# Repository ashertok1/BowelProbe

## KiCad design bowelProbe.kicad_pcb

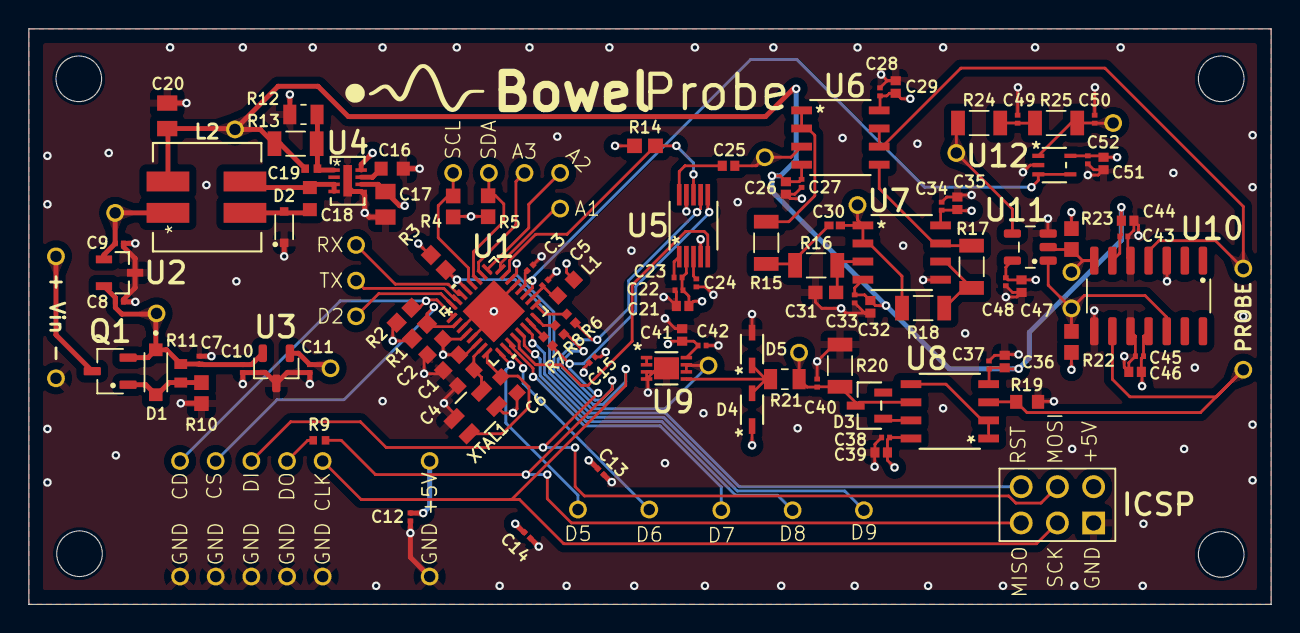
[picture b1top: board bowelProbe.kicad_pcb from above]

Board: 4 copper layers, 87.1 x 40.4 mm, 130 parts (0 on the bottom side), 64 nets.

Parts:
A1, A2, A3: Conn_01x01; CT3149-0
C1, C2, C16, C18: 1u; Cap1uF
C3, C5, C7, C8, C9, C10, C11, C12, C13, C14, C15, C22, C23, C24, C27, C28, C33, C34, C37, C38, C40, C42, C43, C45, C48, C49, C50, C52: 0.1u; Cap0.1uF
C4, C6: 18p; Cap18pF
C17, C20: 4.7u; Cap4.7uF
C19: 4.7p; Cap4.7pF
C21, C25, C26, C29, C32, C35, C36, C39, C41, C44, C46, C47, C51: 10u; Cap10uF
C30: 2.2n; Cap2.2nF
C31: 1n; Cap1nF
D1: BZT52B12
D2: SchottkyDiode; SchottkyReplacement
D2#2, D5, D6, D7, D8, D9: Conn_01x01; CT3149-0
D3: DiodeLowLeak
D4, D5#2: DiodeClamper
ICSP: Conn_02x03_Odd_Even; Dupont2x3
J1, J2: Conn_01x08; microSD
J17: Conn_01x01; CT3149-0
J18, J19, J20, J21, J22, J23, J24, J27, J28, J29, J30, J31, J32: Conn_01x01; CT3149-2
J25, J26: Conn_01x01; CT3149-5
L1: 10u; Inductor10uH
L2: SRF0703-4R7M; Inductor4.7uReplacement
Q1: AO3407A
R1, R2, R3, R4, R5, R10, R14, R22, R23: 10k; Resistor10k
R6, R7, R8, R9: 47; Resistor47
R11: 100k; Resistor100k
R12: 71.5k; Resistor71.5k
R13: 1M; Resistor1M
R15, R16: 6.8k; Resistor6.8k
R17, R24, R25: 30k; Resistor30k
R18: 1.8k; Resistor1.8k
R19: 100; Resistor100
R20: 300k; Resistor300k
R21: 1k; Resistor1k
RX: Conn_01x01; CT3149-0
SCL: Conn_01x01; CT3149-0
SDA: Conn_01x01; CT3149-0
TX: Conn_01x01; CT3149-0
U1: ATmega328P
U2: LM3480IM3-12/NOPB; LM3480IM3-12_NOPB
U3: TLV76050DBZR
U4: LT8330
U5: AD9833BRMZ; AD9833
U6, U8: TL072ACDR; TL072smd
U7: OPA2134UA/2K5; OPA2134smd
U9: MCP6002T-E/MC; MCP6002smd
U10: LM319MX/NOPB; LM319MX_NOPB
U11: SN74LVC1G86DBVR
U12: Buffer
XTAL1: TSX-3225 16.0000MF18X-AC3; Crystal16MHz

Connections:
/+5V: C1.1, C2.1, C11.1, C12.1, C13.1, C14.1, C15.1, C21.1, C22.1, C23.2, C41.1, C42.1, C47.1, C48.1, C51.1, C52.1, D4.1, ICSP.2, J1.1, J21.1, L1.2, R1.1, R2.1, R3.2, R4.2, R5.2, R14.2, R22.2, R23.1, U1.4 (VCC), U1.6 (VCC), U3.1 (OUT), U5.2 (VDD), U9.8 (VDD), U11.5 (Vcc), U12.5 (V+)
/+12V: C9.1, C17.2, C28.2, C29.2, C34.2, C35.2, C38.2, C39.2, C45.1, C46.1, J19.1, L2.1, U2.1 (OUT), U4.6 (VIN), U4.8 (EN/UVLO), U6.8 (VCC+), U7.8 (V+), U8.8 (VCC+), U10.11 (V+)
/-12V: C19.1, C20.2, C26.1, C27.1, C32.1, C33.1, C36.1, C37.1, C43.2, C44.2, J22.1, L2.2, R13.2, U6.4 (VCC-), U7.4 (V-), U8.4 (VCC-), U10.6 (V-)
/A: J30.1, R22.1, U10.12 (OUT1), U11.1 (A)
/A1: A1.1, U1.24 (PC1)
/A2: A2.1, U1.25 (PC2)
/A3: A3.1, U1.26 (PC3)
/B: J29.1, R23.2, U10.7 (OUT2), U11.2 (B)
/CD: J1.8, R2.2, U1.1 (PD3)
/CLKO: U1.12 (CLKO), U5.5 (MCLK)
/D2: D2#2.1, U1.32 (PD2)
/D5: D5.1, U1.9 (PD5)
/D6: D6.1, U1.10 (PD6)
/D7: D7.1, U1.11 (PD7)
/D9: D8.1, U1.13 (PB1)
/D10: D9.1, U1.14 (PB2)
/MISO: ICSP.5, R8.2, R9.2
/MOSI: ICSP.4, J1.6, R7.2, U5.6 (SDATA)
/PDout: C50.2, J32.1, R25.2, U12.1 (+IN)
/PDoutBuf: U1.19 (ADC6), U12.3 (-IN), U12.4 (OUT)
/RX: RX.1, U1.30 (RXD)
/SCK: ICSP.3, J1.4, R6.1, U5.7 (SCLK)
/SCL: R4.1, SCL.1, U1.28 (SCL)
/SDA: R5.1, SDA.1, U1.27 (SDA)
/TX: TX.1, U1.31 (TXD)
/VADC: J28.1, U1.22 (ADC7), U9.6 (VINB-), U9.7 (VOUTB)
/VADCbuf: D4.2, D5#2.1, R21.2, U9.5 (VINB+)
/Vampbuf: J25.1, U6.6 (2IN-), U6.7 (2OUT), U10.4 (+IN1)
/Vamplified: R17.1, U6.5 (2IN+), U7.7 (OUTB)
/Vfiltered: C30.1, J24.1, R18.2, U7.1 (OUTA), U7.2 (INA-)
/Vin: J18.1, Q1.3
/VinReverse: C7.1, C8.1, C10.1, D1.C, J20.1, Q1.2, R11.2, U2.2 (IN), U3.2 (IN)
/Vprobe: J26.1, R19.1, U8.3 (1IN+), U10.9 (+IN2)
/Vsinbuf: R15.1, U6.1 (1OUT), U6.2 (1IN-)
/Vsingen: C25.2, J23.1, U6.3 (1IN+)
/Y: J31.1, R24.1, U11.4 (Y)
/nReset: ICSP.6, R3.1, U1.29 (nRESET)
/nSS: J1.7, R1.2, U1.2 (PD4)
/nSS_Sin: R14.1, U1.23 (PC0), U5.8 (FSYNC)
GND: C1.2, C2.2, C3.2, C4.1, C5.2, C6.1, C7.2, C8.2, C9.2, C10.2, C11.2, C12.2, C13.2, C14.2, C15.2, C16.2, C17.1, C20.1, C21.2, C22.2, C24.1, C26.2, C27.2, C28.1, C29.1, C31.1, C32.2, C33.2, C34.1, C35.1, C36.2, C37.2, C38.1, C39.1, C40.2, C41.2, C42.2, C43.1, C44.1, C45.2, C46.2, C47.2, C48.2, C49.1, C50.1, C51.2, C52.2, D2.C, D5#2.2, ICSP.1, J2.1, J2.4, J2.5, J2.6, J2.7, J2.8, J17.1, R10.1, R12.2, R19.2, R20.2, U1.3 (GND), U1.5 (GND), U1.21 (GND), U1.33 (GND), U2.3 (GND), U3.3 (GND), U4.5 (GND), U4.9 (GND), U5.4 (DGND), U5.9 (AGND), U7.5 (INB+), U9.3 (VINA+), U9.4 (VSS), U9.9 (EPAD), U10.3 (GND1), U10.5 (-IN1), U10.8 (GND2), U10.10 (-IN2), U11.3 (GND), U12.2 (V-), XTAL1.2, XTAL1.4
unnamed: C18.1, D2.A, L2.4
unnamed: C18.2, L2.3, U4.3 (SW), U4.4 (SW)
unnamed: C30.2, R15.2, R16.1
unnamed: C49.2, R24.2, R25.1
unnamed: D1.A, Q1.1, R10.2, R11.1
unnamed: J1.5, R9.1
unnamed: C40.1, D3.3, J27.1, R20.1, R21.1, U8.6 (2IN-)
unnamed: C3.1, U1.20 (AREF)
unnamed: C5.1, L1.1, U1.18 (AVCC)
unnamed: R7.1, U1.15 (MOSI)
unnamed: R8.1, U1.16 (MISO)
unnamed: R6.2, U1.17 (SCK)
unnamed: C4.2, U1.7 (XTAL1), XTAL1.1
unnamed: C6.2, U1.8 (XTAL2), XTAL1.3
unnamed: C19.2, R12.1, R13.1, U4.1 (FBX)
unnamed: C16.1, U4.7 (INTVCC)
unnamed: C24.2, U5.3 (CAP/2.5V)
unnamed: C23.1, U5.1 (COMP)
unnamed: C25.1, U5.10 (VOUT)
unnamed: C31.2, R16.2, U7.3 (INA+)
unnamed: R17.2, R18.1, U7.6 (INB-)
unnamed: U8.1 (1OUT), U8.2 (1IN-), U8.5 (2IN+)
unnamed: D3.1, U8.7 (2OUT)
unnamed: U9.1 (VOUTA), U9.2 (VINA-)

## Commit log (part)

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2026-01-12 init commit
2026-01-16 Schematic Updates
    Found exact parts for op amps and diode. Imported their symbols, footprints, and .step files. Corrected various wiring mistakes.
    To do:
    - Add 0-5V voltage control/clamping at RC output
    - Add buffer following this clamping circuit
    - Connect all +5V to each other, -12V to each other, etc.
    - Find/determine footprints for all other parts (design if have to)
2026-01-19 PCB Finalized
    Finished PCB layout and routing. Awaiting final check.
2026-01-20 Finished PCB
    Re-did layout, routing, via placement / stitching, copper pours. Added a wordmark.
    To do:
    - Nothing else unless we want to delete and/or modify references
2026-03-23 Finished Electronic Schematic, Awaiting Finalizations and Review
    Added many symbols, footprints, and 3d models. Organized design into functional blocks.
    Still need finalized plans and footprints for "demo".
    Next Steps:
    - Finalize "demo" subciruit
    - Review schematic
    - Move on to layout
2026-03-23 Schematic Finalized and Reviewed, Awaiting Professor Review
    Schematic finalized, corrected, and finished. Awaiting professor review.
    Next steps:
    - PCB layout
    - Programming
    - Update BOM
2026-03-25 LTspice Source Scripting
    Created python script to model sine wave generator (replacement model for chip AD9833 w/o spice model). Additionally began initial pcb placement.
2026-03-27 LTspice Simulations
    Necessary LTspice Simulation models and files included in subdirectory "LTspiceSim" of BowelProbe. Simulated power rail generation and the various stages of the analog circuit.
2026-03-27 KiCad Updates
    Added buffer after wave AD9833 sine generation and coupling capacitor (as simulated in LTspice) to address loading on filter stage. Added symbol, footprint, 3D model, and spice model in corresponding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
    Updated BOM with this new part and updated PCB layout with buffer parts.
2026-03-28 PCB Layout Progress
    Initial rough layout of parts into corresponding sections. Next up is to formalize signal, power, and SPI flow as well as specific component placements.
2026-03-29 Schematic and Layout Updates
    Added 47 ohm resistors to schematic to reduce ringing of SPI through ports and added corresponding info to BOM. Set PCB layout. May make a few more small tweaks.
2026-03-29 PCB Layout Plan Finalized
    Added more stitching capacitors in schematic. Decided on final layout and added necessary vias. Added NPTH M3 mounting holes.
2026-03-30 PCB Layout Routed
    Schematic references adjusted and extra stitching capacitors removed. Layout added a few vias and fully routed.
    Layout Finalization:
    - Add ground pours on L1 and L4
    - Add stitching vias
    - Add edge stitching vias
    - Review
2026-03-30 PCB Finished
    Added pours and stitching to finish layout. Adjusted BOM to fit JLCPCB expected. Generated CPL file. Various KiCad plugins were downloaded. A folder "PCBA_Files" created to hold BOM, Pick and Place, 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
    Final Objectives:
    - Simulate with Ansys HFSS
2026-03-30 Slight BOM Adjustments
2026-03-30 HFSS File Generation
    Various files generated to be imported into Ansys HFSS for simulation
2026-03-30 Updated Simulation Files
2026-03-30 EMI Simulation Updates
    DXF file imported. Layers were organized and materials were assigned
2026-03-31 Part Replacement
    Replaced Coilcraft inductor for an in stock part. Adjusted PCBA files accordingly.
2026-03-31 Part Replacements
    Replaced crystal and schottky diode. Adjusted schematic, PCB, and BOM accordingly. Organized schematic and colored different sections.
2026-03-31 Fully Reviewed and Cleared For Immediate Order
2026-03-31 Update .gitignore
    Show PCBA csvs
2026-03-31 Commit PCBA File CSVs
2026-04-01 Gitignore for giant 3D step file
2026-04-01 Bowel Probe Images
2026-05-03 HFSS Post-Layout Verification Files
    Generated IPC-2581 and ODB++ files for easy import of PCB and simulation.
2026-06-26 Revision 1 Initial Updates
    - Removed heatsink
    - Swapped 5V regulator for SMT version
    - Added 12V regulation
    - Adjusted regulator input/output capacitors according to datasheets
    - Swapped buffer for TL072 and added buffer stage between amplification and voltage divider stages
    - Fixed decoupling cap issue on V- rail of buffer between sine generation and filtering
2026-06-27 Rev 1 Progress
    - Updated BOM for the SMT +12V and +5V regulators
    - Removed tracks from previous board
    - Deleted heatsink and +5V THT regulator from layout
    - Set an initial layout plan (~80% complete)
    - Updated various silkscreens to signal the proper part and orientation
    - Updated silkscreen for Vin, I2C, and UART pins
2026-06-28 Initial Layout (Rev 1)
    Initial layout plan nearly complete. Needs positioning of test points and stitching capacitors as well as any additional vias afterwards. Also considering making available more ATMega channels as spa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
